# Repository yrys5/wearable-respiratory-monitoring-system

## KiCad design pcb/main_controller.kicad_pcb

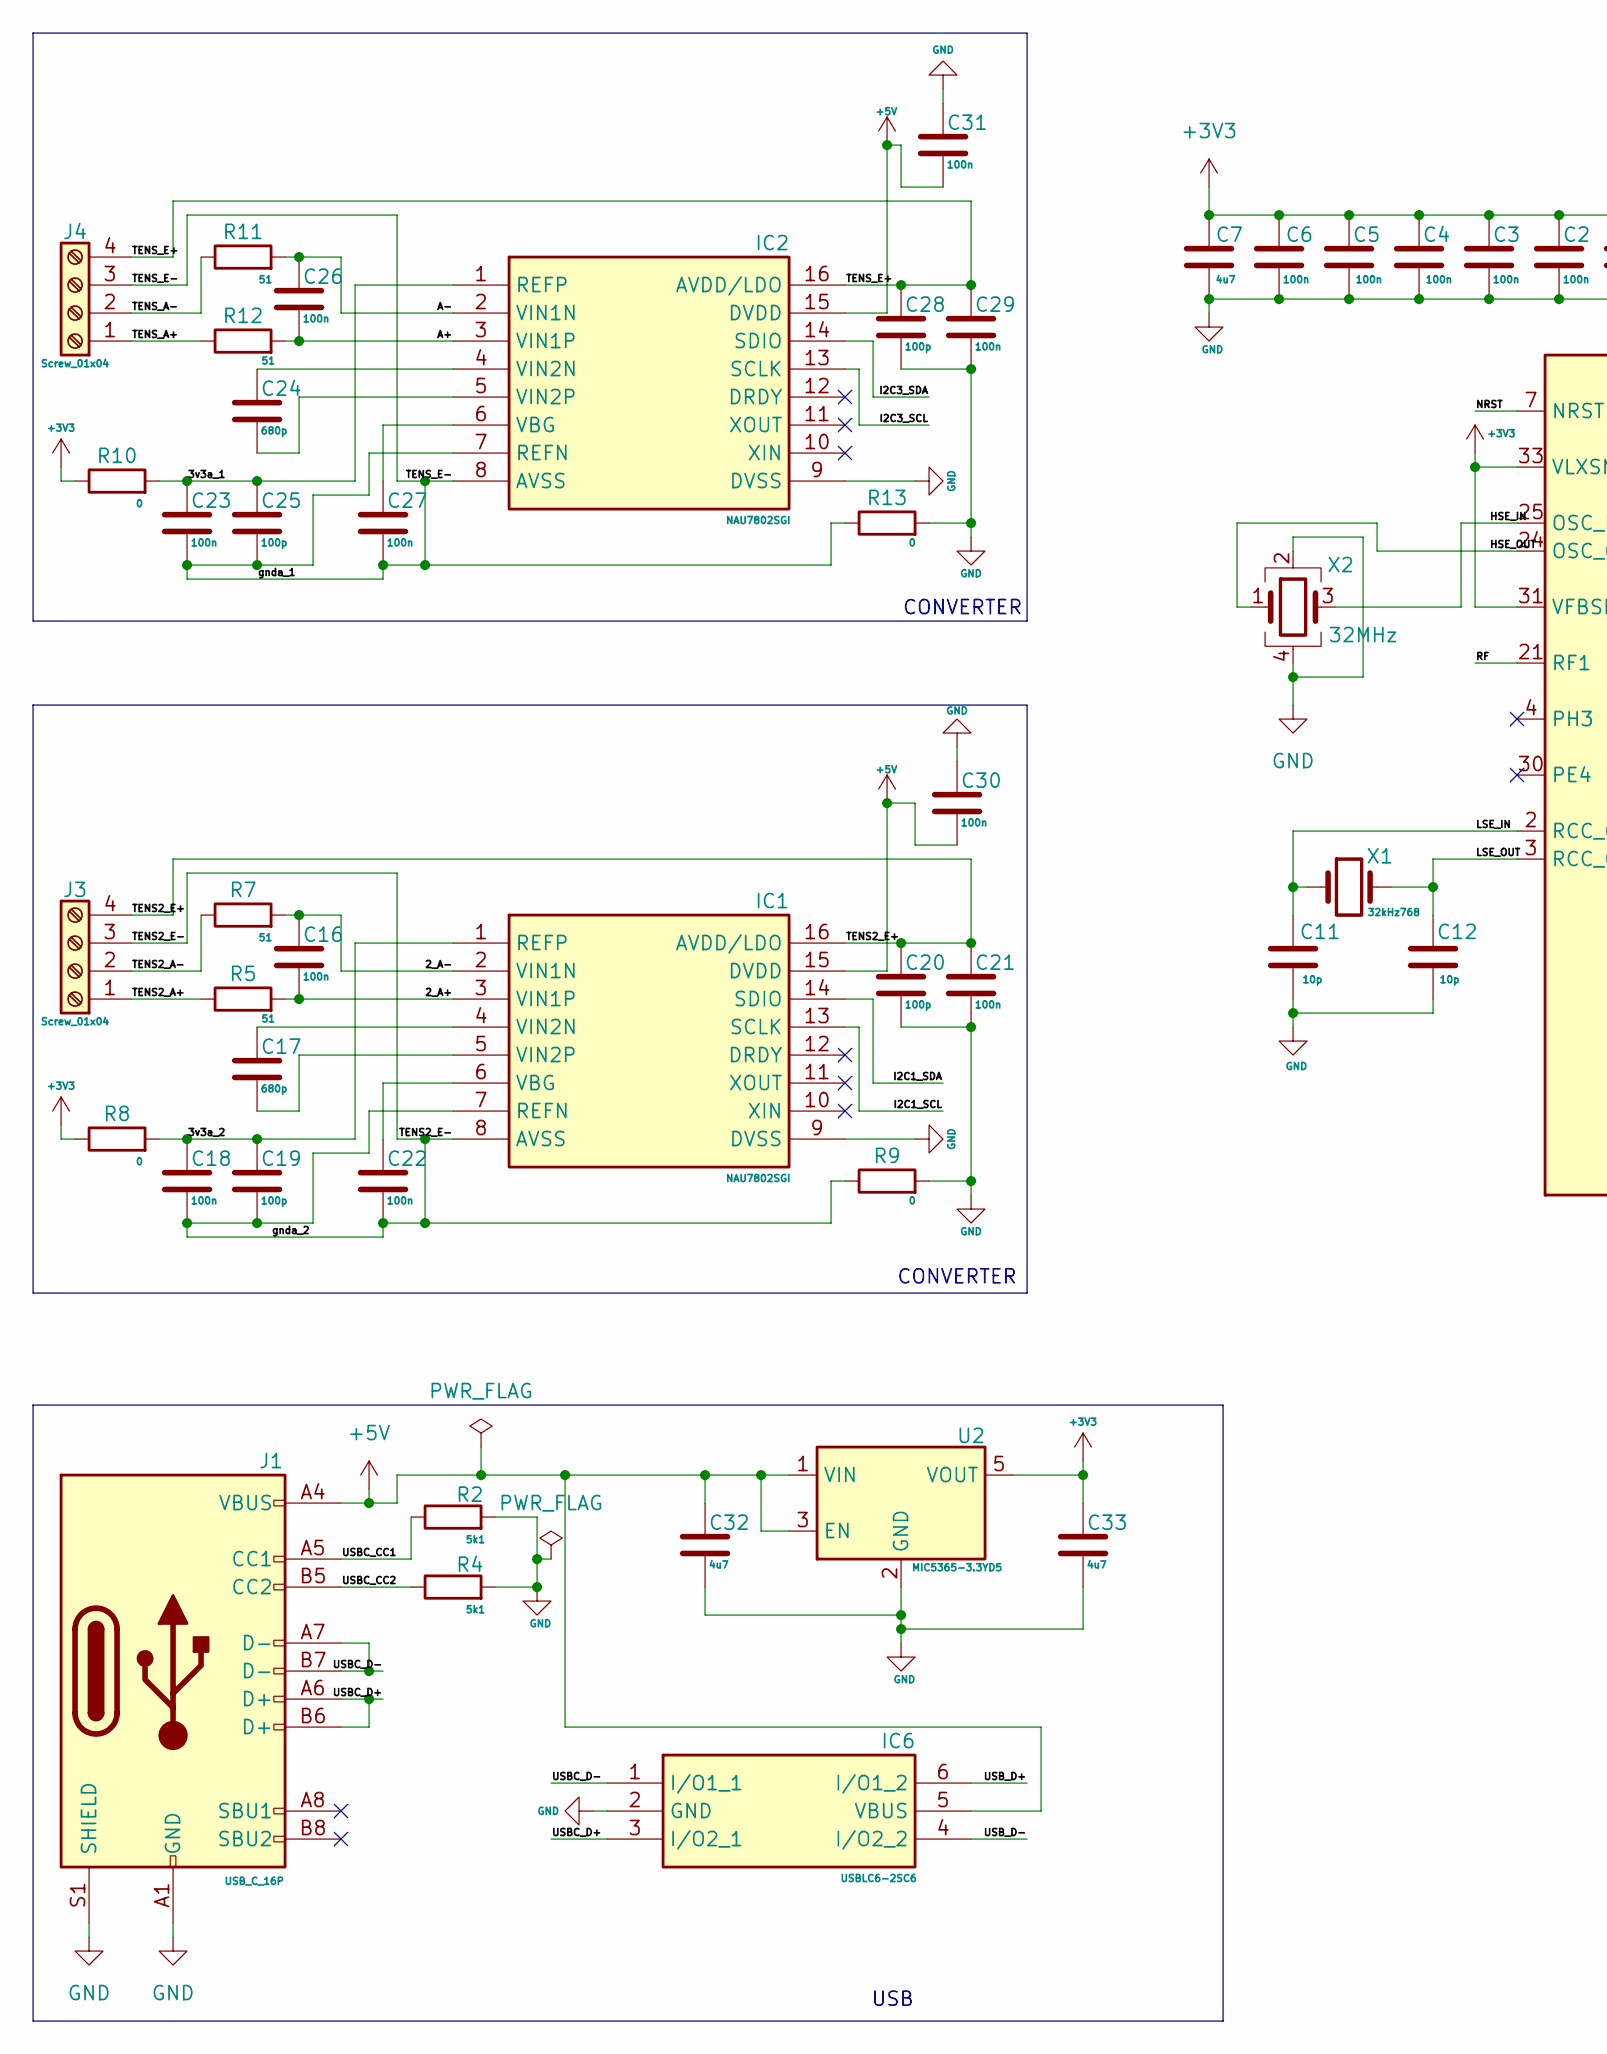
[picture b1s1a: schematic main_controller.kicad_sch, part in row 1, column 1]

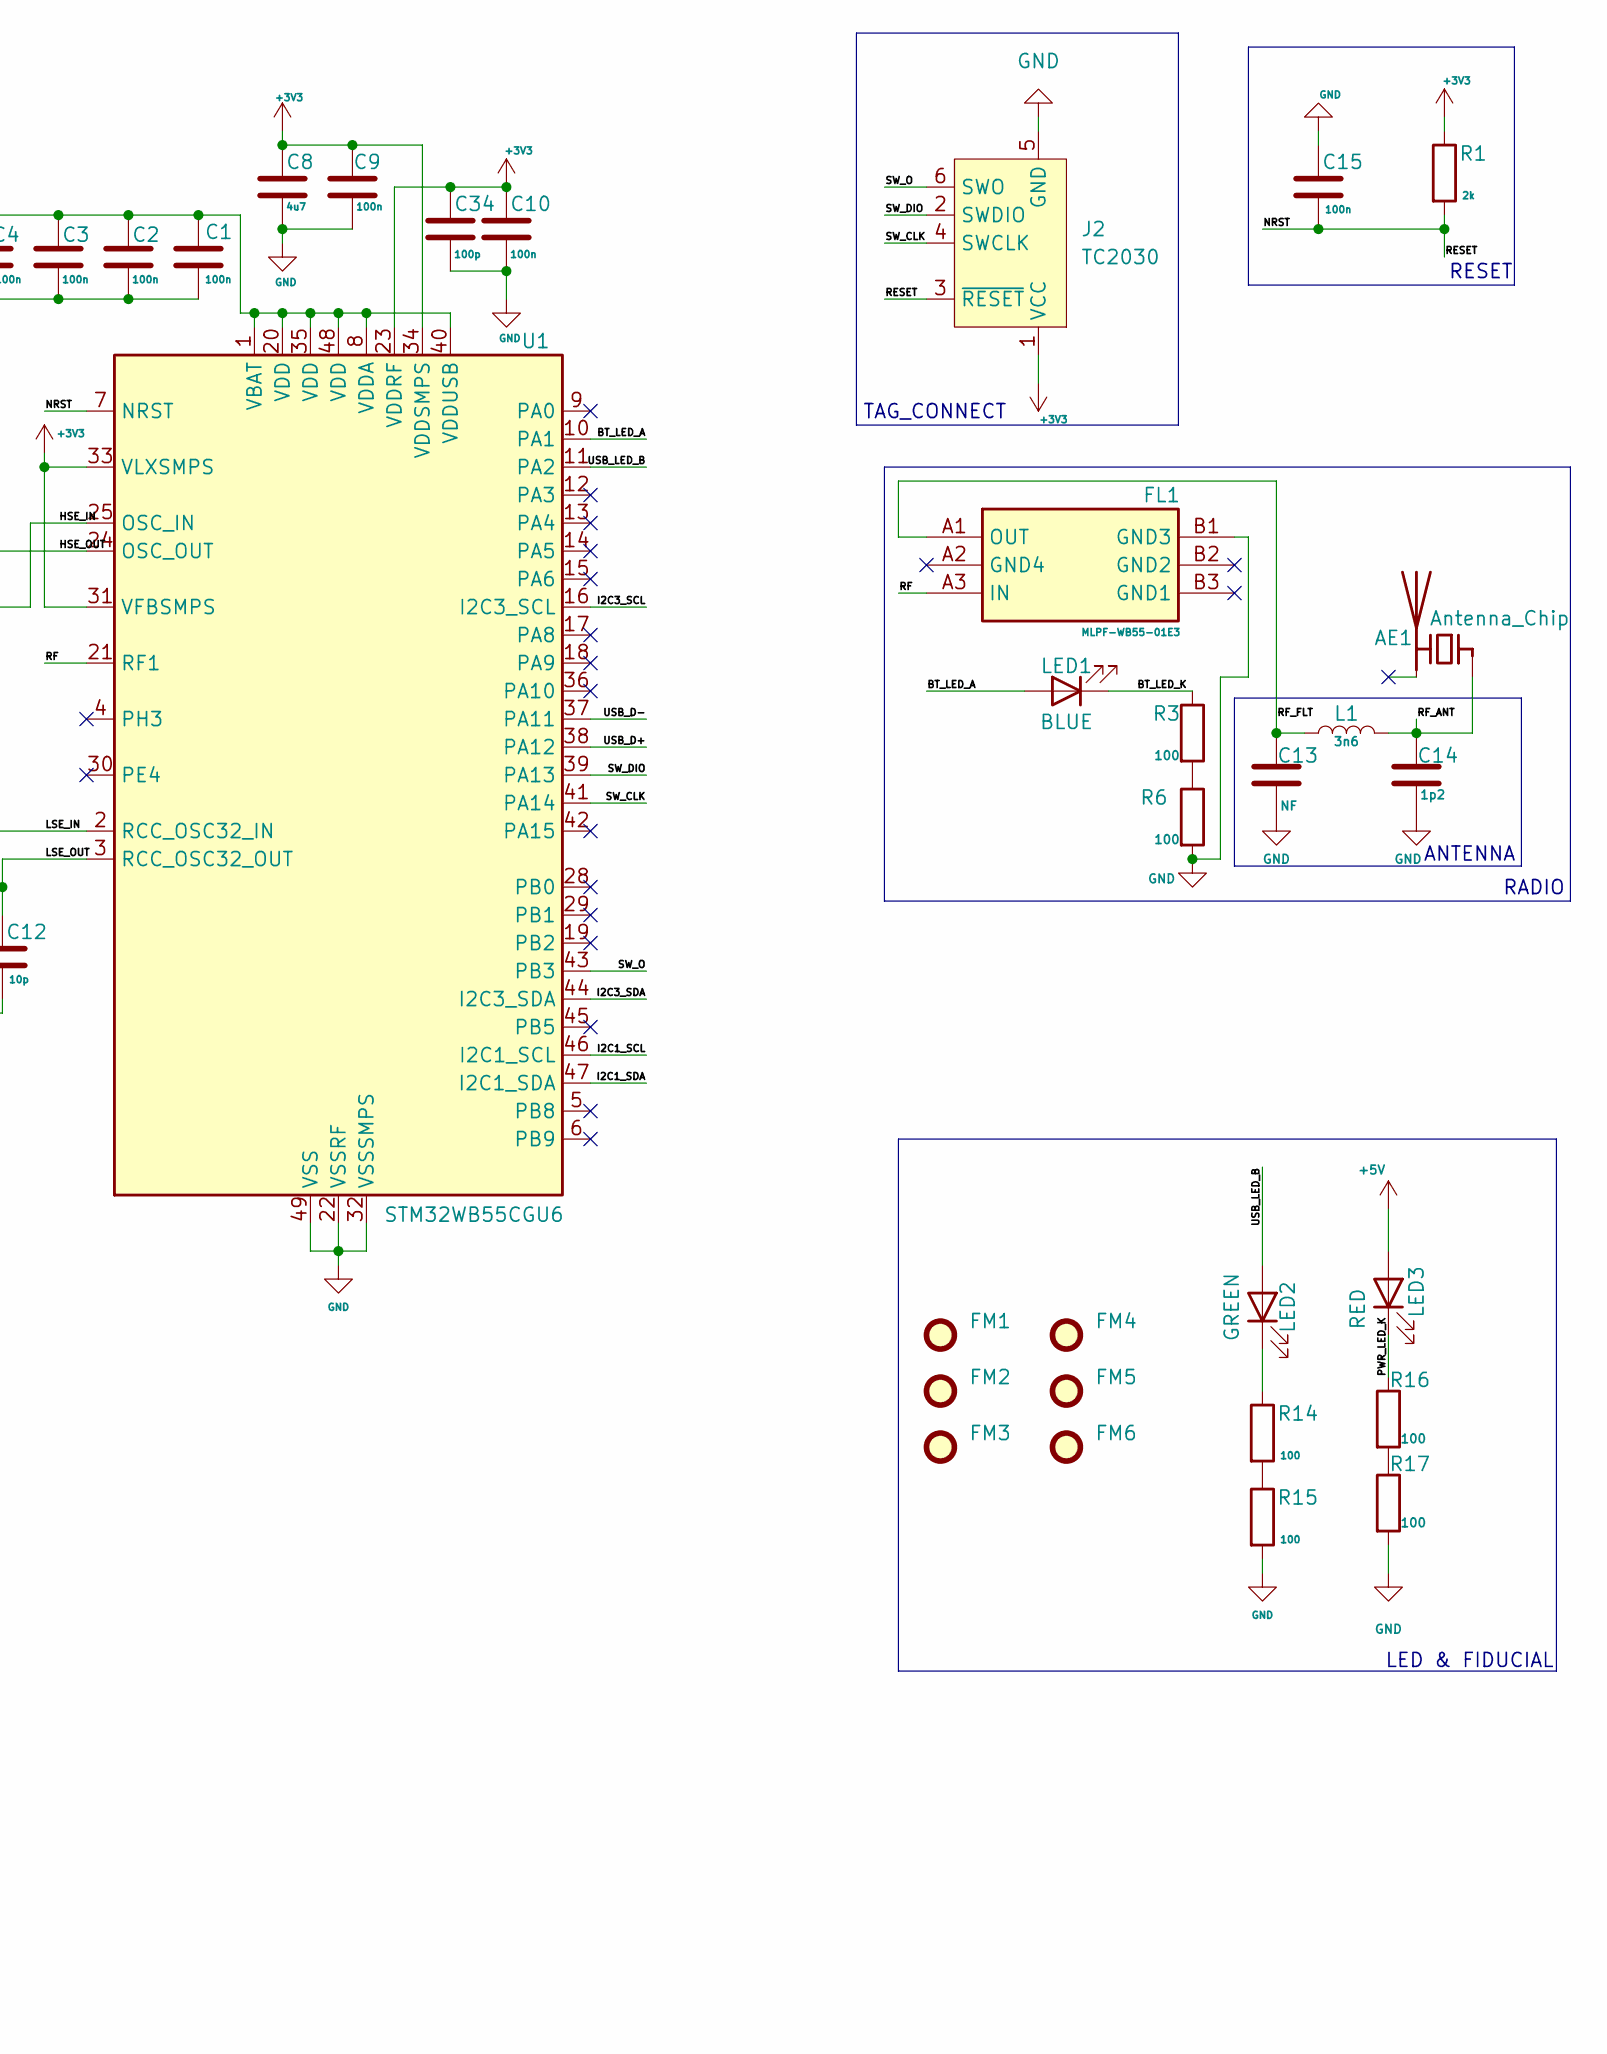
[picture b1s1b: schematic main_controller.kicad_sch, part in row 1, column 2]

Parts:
AE1: Antenna_Chip; ANT3216LL00R2400A; Manufacturer_Part_Number ANT3216LL00R2400A
C1, C2, C3, C4, C5, C6, C9, C10, C15, C16, C18, C21, C22, C23, C26, C27, C29, C30, C31: 100n; C_0402_1005Metric; Manufacturer_Part_Number 04023C104KAT2A
C7, C8, C32, C33: 4u7; C_0603_1608Metric; Manufacturer_Part_Number 0603YD475MAT2A
C11, C12: 10p; C_0402_1005Metric; Manufacturer_Part_Number 04025A100JAT4A
C13: NF; C_0402_1005Metric; Manufacturer_Part_Number 04023A102KAT2A
C14: 1p2; C_0402_1005Metric; Manufacturer_Part_Number 04025U1R2CAT2A; DigiKey Number 490-6210-1-ND
C17, C24: 680p; C_0402_1005Metric; Manufacturer_Part_Number KGM05ACG1H681JH
C19, C20, C25, C28, C34: 100p; C_0402_1005Metric; Manufacturer_Part_Number KGM05ACG1E101JH
FL1: MLPF-WB55-01E3; BUMPLESS_CSP_2025; Mouser Part Number 511-MLPF-WB55-01E3
FM1, FM2, FM3, FM4, FM5, FM6: Fiducial; Fiducial_1mm_Mask2mm
IC1, IC2: NAU7802SGI; SOIC127P600X175-16N; Manufacturer_Part_Number NAU7802SGI
IC6: USBLC6-2SC6; SOT95P280X145-6N; Mouser Part Number 511-USBLC6-2SC6
J1: USB_C_16P; USB_C_Receptacle_GCT_USB4105-xx-A_16P_TopMnt_Horizontal; Manufacturer_Part_Number USB4105-GF-A
J2: TC2030; Tag-Connect_TC2030-IDC-FP_2x03_P1.27mm_Vertical
J3, J4: Screw_01x04; 2828374; Manufacturer_Part_Number 282837-4
L1: 3n6; L_0402_1005Metric; Manufacturer_Part_Number LQG15HH3N6S02D; DigiKey Number 490-6571-1-ND
LED1: BLUE; LED_0603_1608Metric; Manufacturer_Part_Number 150040BS73240
LED2: GREEN; LED_0603_1608Metric; Manufacturer_Part_Number 150040GS73240
LED3: RED; LED_0603_1608Metric; Manufacturer_Part_Number 150040RS73240; DigiKey Number 160-1447-1-ND
R1: 2k; R_0402_1005Metric; Manufacturer_Part_Number RC0402JR-072KP
R2, R4: 5k1; R_0402_1005Metric; Manufacturer_Part_Number RC0402FR-075K1L
R3, R6, R16, R17: 100; R_0402_1005Metric; Manufacturer_Part_Number RC0402FR-7D100RL; DigiKey Number 311-100JRCT-ND
R5, R7, R11, R12: 51; R_0402_1005Metric; Manufacturer_Part_Number RC0402FR-0751RL
R8, R9, R10, R13: 0; R_0402_1005Metric; Manufacturer_Part_Number RC0402JR-7D0RL
R14, R15: 100; R_0402_1005Metric; Manufacturer_Part_Number RC0402FR-7D100RL
U1: STM32WB55CGU6; QFN-48-1EP_7x7mm_P0.5mm_EP5.6x5.6mm; Manufacturer_Part_Number STM32WB55CGU6
U2: MIC5365-3.3YD5; TSOT-23-5; Manufacturer_Part_Number MIC5365-3.3YD5-TR
X1: 32kHz768; Crystal_SMD_2012-2Pin_2.0x1.2mm; Manufacturer_Part_Number NX2012SA-32.768K-STD-MUB-1
X2: 32MHz; Crystal_SMD_2016-4Pin_2.0x1.6mm; Manufacturer_Part_Number NX2016SA-32M-EXS00A-CS06465

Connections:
+3V3: C1.1, C2.1, C3.1, C4.1, C5.1, C6.1, C7.1, C8.1, C9.1, C10.1, C33.1, C34.1, J2.1 (VCC), R1.1, R8.1, R10.1, U1.1 (VBAT), U1.8 (VDDA), U1.20 (VDD), U1.23 (VDDRF), U1.31 (VFBSMPS), U1.33 (VLXSMPS), U1.34 (VDDSMPS), U1.35 (VDD), U1.40 (VDDUSB), U1.48 (VDD), U2.5 (VOUT)
+5V: C30.2, C31.2, C32.1, IC1.15 (DVDD), IC2.15 (DVDD), IC6.5 (VBUS), J1.A4 (VBUS), J1.A9 (VBUS), J1.B4 (VBUS), J1.B9 (VBUS), LED3.2 (A), U2.1 (VIN), U2.3 (EN)
/2_A+: C16.2, IC1.3 (VIN1P), R5.2
/2_A-: C16.1, IC1.2 (VIN1N), R7.2
/3v3a_1: C23.1, C25.1, IC2.1 (REFP), R10.2
/3v3a_2: C18.1, C19.1, IC1.1 (REFP), R8.2
/A+: C26.2, IC2.3 (VIN1P), R12.2
/A-: C26.1, IC2.2 (VIN1N), R11.2
/BT_LED_A: LED1.2 (A), U1.10 (PA1)
/BT_LED_K: LED1.1 (K), R3.1
/HSE_IN: U1.25 (OSC_IN), X2.3
/HSE_OUT: U1.24 (OSC_OUT), X2.1
/I2C1_SCL: IC1.13 (SCLK), U1.46 (I2C1_SCL)
/I2C1_SDA: IC1.14 (SDIO), U1.47 (I2C1_SDA)
/I2C3_SCL: IC2.13 (SCLK), U1.16 (I2C3_SCL)
/I2C3_SDA: IC2.14 (SDIO), U1.44 (I2C3_SDA)
/LSE_IN: C11.1, U1.2 (RCC_OSC32_IN), X1.1
/LSE_OUT: C12.1, U1.3 (RCC_OSC32_OUT), X1.2
/NRST: C15.2, J2.3 (~RESET), R1.2, U1.7 (NRST)
/PWR_LED_K: LED3.1 (K), R16.1
/RF: FL1.A3 (IN), U1.21 (RF1)
/RF_ANT: AE1.1 (FEED), C14.1, L1.2
/RF_FLT: C13.1, FL1.A1 (OUT), L1.1
/SW_CLK: J2.4 (SWCLK), U1.41 (PA14)
/SW_DIO: J2.2 (SWDIO), U1.39 (PA13)
/SW_O: J2.6 (SWO), U1.43 (PB3)
/TENS2_A+: J3.1, R5.1
/TENS2_A-: J3.2, R7.1
/TENS2_E+: C20.1, C21.1, IC1.16 (AVDD/LDO), J3.4
/TENS2_E-: C18.2, C19.2, C22.2, IC1.7 (REFN), IC1.8 (AVSS), J3.3, R9.1
/TENS_A+: J4.1, R12.1
/TENS_A-: J4.2, R11.1
/TENS_E+: C28.1, C29.1, IC2.16 (AVDD/LDO), J4.4
/TENS_E-: C23.2, C25.2, C27.2, IC2.7 (REFN), IC2.8 (AVSS), J4.3, R13.1
/USBC_CC1: J1.A5 (CC1), R2.1
/USBC_CC2: J1.B5 (CC2), R4.1
/USBC_D+: IC6.3 (I/O2_1), J1.A6 (D+), J1.B6 (D+)
/USBC_D-: IC6.1 (I/O1_1), J1.A7 (D-), J1.B7 (D-)
/USB_D+: IC6.6 (I/O1_2), U1.38 (PA12)
/USB_D-: IC6.4 (I/O2_2), U1.37 (PA11)
GND: C1.2, C2.2, C3.2, C4.2, C5.2, C6.2, C7.2, C8.2, C9.2, C10.2, C11.2, C12.2, C13.2, C14.2, C15.1, C20.2, C21.2, C28.2, C29.2, C30.1, C31.1, C32.2, C33.2, C34.2, FL1.B1 (GND3), IC1.9 (DVSS), IC2.9 (DVSS), IC6.2 (GND), J1.A1 (GND), J1.A12 (GND), J1.B1 (GND), J1.B12 (GND), J1.S1 (SHIELD), J2.5 (GND), R2.2, R4.2, R6.2, R9.2, R13.2, R15.2, R17.2, U1.22 (VSSRF), U1.32 (VSSSMPS), U1.49 (VSS), U2.2 (GND), X2.2, X2.4
unnamed: C22.1, IC1.6 (VBG)
unnamed: C17.1, IC1.4 (VIN2N)
unnamed: C17.2, IC1.5 (VIN2P)
unnamed: C27.1, IC2.6 (VBG)
unnamed: C24.1, IC2.4 (VIN2N)
unnamed: C24.2, IC2.5 (VIN2P)
unnamed: LED2.2 (A), U1.11 (PA2)
unnamed: LED2.1 (K), R14.1
unnamed: R3.2, R6.1
unnamed: R14.2, R15.1
unnamed: R16.2, R17.1

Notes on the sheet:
RADIO
CONVERTER
ANTENNA
TAG_CONNECT
RESET
USB
LED & FIDUCIAL

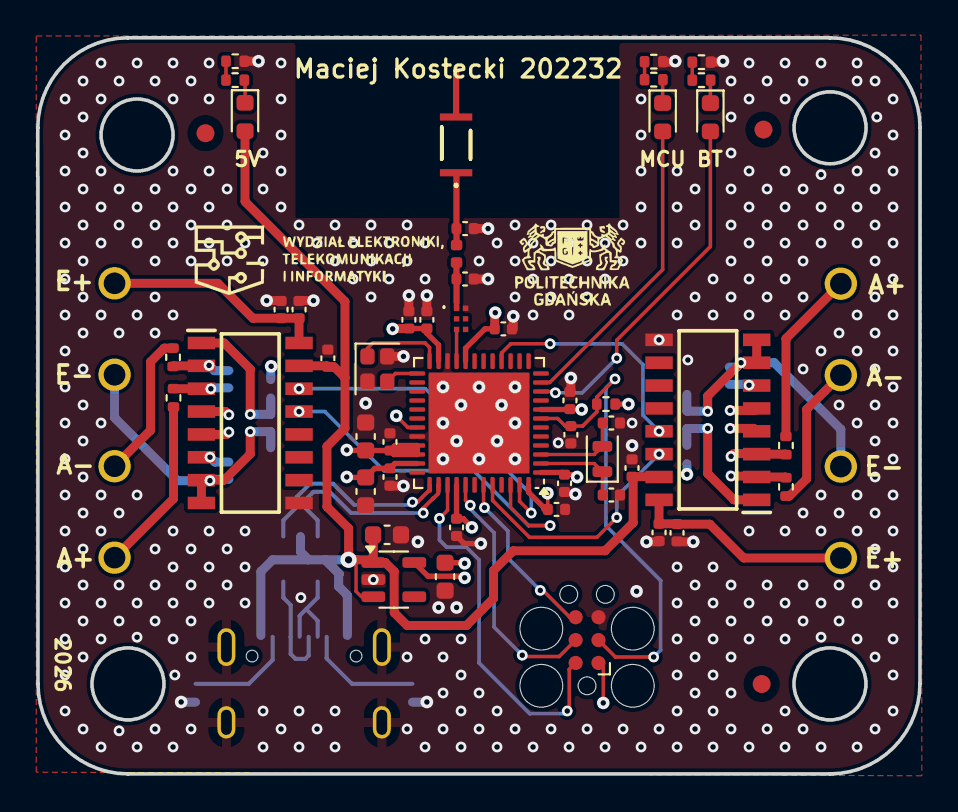
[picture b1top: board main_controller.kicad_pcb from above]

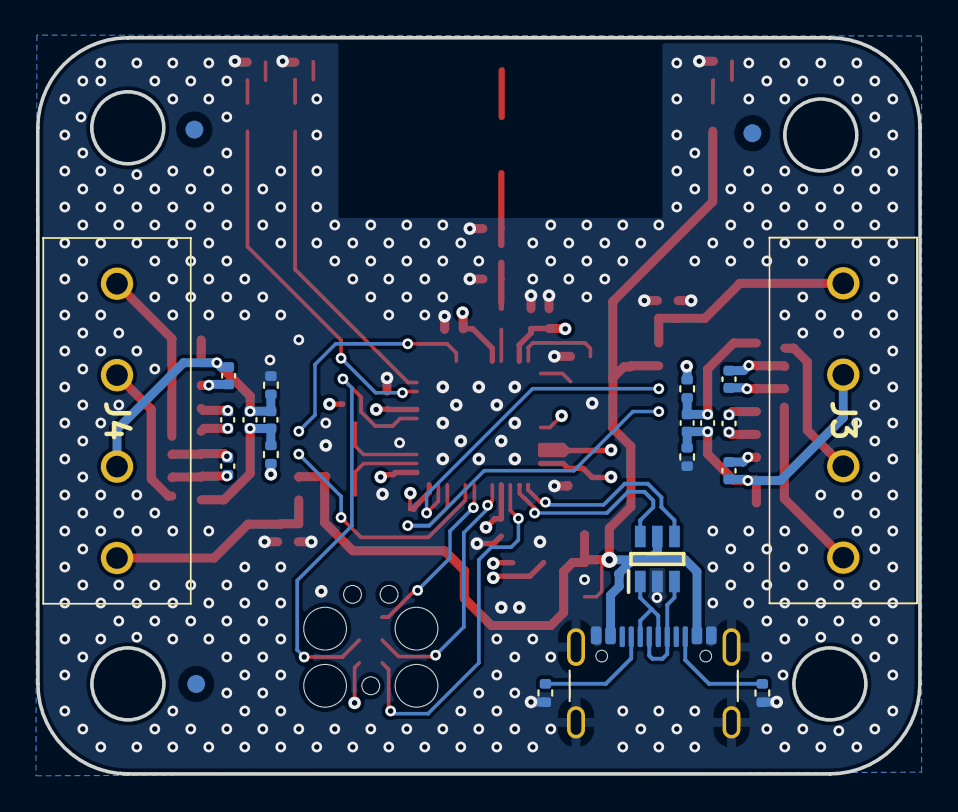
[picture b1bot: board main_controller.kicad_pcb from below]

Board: 4 copper layers, 49.0 x 40.9 mm, 74 parts (23 on the bottom side), 52 nets.

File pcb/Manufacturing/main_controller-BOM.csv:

Reference;Qty;Value;DNP;Exclude from BOM;Exclude from Board;Footprint;Datasheet;Distributor Link;Manufacturer;Manufacturer_Part_Number;Opis
AE1;1;Antenna_Chip;;;;SamacSys_Parts:ANT3216LL00R2400A;~;https://www.mouser.pl/ProductDetail/Pulse-Electronics/ANT321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;Pulse Electronics;ANT3216LL00R2400A;Ceramic chip antenna with pin for PCB trace
C1,C2,C3,C4,C5,C6,C9,C10,C15,C16,C18,C21,C22,C23,C26,C27,C29,C30,C31;19;100n;;;;Capacitor_SMD:C_0402_1005Metric;~;https://www.mouser.pl/ProductDetail/KYOCERA-AVX/04023C104KAT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;KYOCERA AVX;04023C104KAT2A;Unpolarized capacitor
C7,C8,C32,C33;4;4u7;;;;Capacitor_SMD:C_0603_1608Metric;~;https://www.mouser.pl/ProductDetail/KYOCERA-AVX/0603YD475MAT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;KYOCERA AVX;0603YD475MAT2A  ;Unpolarized capacitor
C11,C12;2;10p;;;;Capacitor_SMD:C_0402_1005Metric;~;https://www.mouser.pl/ProductDetail/KYOCERA-AVX/04025A100JAT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; KYOCERA AVX;04025A100JAT4A;Unpolarized capacitor
C13;1;NF;;;;Capacitor_SMD:C_0402_1005Metric;~;https://www.mouser.pl/ProductDetail/KYOCERA-AVX/04023A102KAT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; KYOCERA AVX;04023A102KAT2A;Unpolarized capacitor
C14;1;1p2;;;;Capacitor_SMD:C_0402_1005Metric;~;https://www.mouser.pl/ProductDetail/KYOCERA-AVX/04025U1R2CAT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; KYOCERA AVX;04025U1R2CAT2A;Unpolarized capacitor
C17,C24;2;680p;;;;Capacitor_SMD:C_0402_1005Metric;~;https://www.mouser.pl/ProductDetail/KYOCERA-AVX/KGM05ACG1H68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; KYOCERA AVX;KGM05ACG1H681JH;Unpolarized capacitor
C19,C20,C25,C28,C34;5;100p;;;;Capacitor_SMD:C_0402_1005Metric;~;https://www.mouser.pl/ProductDetail/KYOCERA-AVX/KGM05ACG1E10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; KYOCERA AVX;KGM05ACG1E101JH;Unpolarized capacitor
FL1;1;MLPF-WB55-01E3;;;;SamacSys_Parts:BUMPLESS_CSP_2025;https://www.st.com/resource/en/datasheet/mlpf-wb55-01e3.pdf;https://www.mouser.pl/ProductDetail/STMicroelectronics/MLPF-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;STMicroelectronics;MLPF-WB55-01E3;2.4 GHz low pass filter matched to STM32WB55Cx/Rx, STM32WB50Cx, STM32WB35Cx and STM32WB30Cx
FM1,FM2,FM3,FM4,FM5,FM6;6;Fiducial;;Excluded from BOM;;Fiducial:Fiducial_1mm_Mask2mm;~;;;;Fiducial Marker
IC1,IC2;2;NAU7802SGI;;;;SamacSys_Parts:SOIC127P600X175-16N;https://www.nuvoton.com/resource-files/NAU7802%20Data%20Shee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;https://www.mouser.pl/ProductDetail/Nuvoton/NAU7802SGI?qs=A6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;Nuvoton;NAU7802SGI;24 Bit Analog to Digital Converter 2 Input 1 Sigma-Delta 16-SOP
IC6;1;USBLC6-2SC6;;;;SamacSys_Parts:SOT95P280X145-6N;https://www.st.com/resource/en/datasheet/usblc6-2.pdf;https://www.mouser.pl/ProductDetail/STMicroelectronics/USBLC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;STMicroelectronics;USBLC6-2SC6;TVS Diode Array Uni-Directional USBLC6-2SC6 17V, SOT-23 6-Pin
J1;1;USB_C_16P;;;;Connector_USB:USB_C_Receptacle_GCT_USB4105-xx-A_16P_TopMnt_Horizontal;https://www.usb.org/sites/default/files/documents/usb_type-c.zip;https://www.mouser.pl/ProductDetail/GCT/USB4105-GF-A?qs=KUoI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;GCT;USB4105-GF-A;USB 2.0-only 16P Type-C Receptacle connector
J2;1;TC2030;;Excluded from BOM;;Connector:Tag-Connect_TC2030-IDC-FP_2x03_P1.27mm_Vertical;https://www.tag-connect.com/wp-content/uploads/bsk-pdf-manag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;;;;Tag-Connect ARM Cortex SWD JTAG connector, 6 pin
J3,J4;2;Screw_01x04;;;;SamacSys_Parts:2828374;~;https://www.mouser.pl/ProductDetail/TE-Connectivity/282837-4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;TE Connectivity;282837-4;Generic screw terminal, single row, 01x04, script generated (kicad-library-utils/schlib/autogen/connector/)
L1;1;3n6;;;;Inductor_SMD:L_0402_1005Metric;~;https://www.mouser.pl/ProductDetail/Murata-Electronics/LQG15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;Murata Electronics;LQG15HH3N6S02D;Inductor
LED1;1;BLUE;;;;LED_SMD:LED_0603_1608Metric;~;https://www.mouser.pl/ProductDetail/Wurth-Elektronik/150040B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; Wurth Elektronik;150040BS73240;Light emitting diode
LED2;1;GREEN;;;;LED_SMD:LED_0603_1608Metric;~;https://www.mouser.pl/ProductDetail/Wurth-Elektronik/150040G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; Wurth Elektronik;150040GS73240;Light emitting diode
LED3;1;RED;;;;LED_SMD:LED_0603_1608Metric;~;https://www.mouser.pl/ProductDetail/Wurth-Elektronik/150040R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; Wurth Elektronik;150040RS73240;Light emitting diode
R1;1;2k;;;;Resistor_SMD:R_0402_1005Metric;~;https://www.mouser.pl/ProductDetail/YAGEO/RC0402JR-072KP?qs=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;YAGEO;RC0402JR-072KP;Resistor
R2,R4;2;5k1;;;;Resistor_SMD:R_0402_1005Metric;~;https://www.mouser.pl/ProductDetail/YAGEO/RC0402FR-075K1L?qs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;YAGEO;RC0402FR-075K1L;Resistor
R3,R6,R14,R15,R16,R17;6;100;;;;Resistor_SMD:R_0402_1005Metric;~;https://www.mouser.pl/ProductDetail/YAGEO/RC0402FR-7D100RL?q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;YAGEO;RC0402FR-7D100RL;Resistor
R5,R7,R11,R12;4;51;;;;Resistor_SMD:R_0402_1005Metric;~;https://www.mouser.pl/ProductDetail/YAGEO/RC0402FR-0751RL?qs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;YAGEO;RC0402FR-0751RL;Resistor
R8,R9,R10,R13;4;0;;;;Resistor_SMD:R_0402_1005Metric;~;https://www.mouser.pl/ProductDetail/YAGEO/RC0402JR-7D0RL?qs=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;YAGEO;RC0402JR-7D0RL;Resistor
U1;1;STM32WB55CGU6;;;;Package_DFN_QFN:QFN-48-1EP_7x7mm_P0.5mm_EP5.6x5.6mm;https://www.st.com/resource/en/datasheet/stm32wb55cg.pdf;https://www.mouser.pl/ProductDetail/STMicroelectronics/STM32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;STMicroelectronics;STM32WB55CGU6;STMicroelectronics Arm Cortex-M4 MCU, 1024KB flash, 256KB RAM, 64 MHz, 1.71-3.6V, 30 GPIO, UFQFPN48
U2;1;MIC5365-3.3YD5;;;;Package_TO_SOT_SMD:TSOT-23-5;https://ww1.microchip.com/downloads/aemDocuments/documents/A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;https://www.mouser.pl/ProductDetail/Microchip-Technology/MIC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;Microchip Technology;MIC5365-3.3YD5-TR;150mA Low-dropout Voltage Regulator, Vout 3.3V, Vin up to 5.5V, TSOT-23-5
X1;1;32kHz768;;;;Crystal:Crystal_SMD_2012-2Pin_2.0x1.2mm;~;https://www.mouser.pl/ProductDetail/NDK/NX2012SA-32.768K-STD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;NDK;NX2012SA-32.768K-STD-MUB-1;Two pin crystal
X2;1;32MHz;;;;Crystal:Crystal_SMD_2016-4Pin_2.0x1.6mm;~;https://www.mouser.pl/ProductDetail/NDK/NX2016SA-32M-EXS00A-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;NDK;NX2016SA-32M-EXS00A-CS06465;Four pin crystal, GND on pins 2 and 4

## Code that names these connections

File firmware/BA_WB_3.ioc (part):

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Mcu.Name=STM32WB55CGUx
Mcu.Package=UFQFPN48
Mcu.UserName=STM32WB55CGUx
PA1.GPIOParameters=GPIO_Label
PA1.GPIO_Label=BL_LED_A
PA1.Signal=GPIO_Output
PA11.Mode=Device
PA11.Signal=USB_DM
PA12.Mode=Device
PA12.Signal=USB_DP
PA13.Mode=Serial_Wire
PA13.Signal=SYS_JTMS-SWDIO
PA14.Mode=Serial_Wire
PA14.Signal=SYS_JTCK-SWCLK
PA2.GPIOParameters=GPIO_Label
PA2.GPIO_Label=MCU_LED
PA2.Signal=GPIO_Output
PA7.Mode=I2C
PA7.Signal=I2C3_SCL
PB3.Signal=SYS_JTDO-SWO
PB4.Mode=I2C
PB4.Signal=I2C3_SDA
PB6.Mode=I2C
PB6.Signal=I2C1_SCL
PB7.Mode=I2C
PB7.Signal=I2C1_SDA
PC14-OSC32_IN.Mode=LSE-External-Oscillator
PC14-OSC32_IN.Signal=RCC_OSC32_IN
PC15-OSC32_OUT.Mode=LSE-External-Oscillator
PC15-OSC32_OUT.Signal=RCC_OSC32_OUT
RCC.HSE_VALUE=32000000
RCC.SYSCLKFreq_VALUE=64000000
RCC.SYSCLKSource=RCC_SYSCLKSOURCE_PLLCLK
board=custom
